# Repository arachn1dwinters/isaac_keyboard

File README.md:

# isaac_keyboard
This repository contains the .gerber files (which can be sent to a service like JPLPCB for manufacture) and the kicad files themselves for customization purposes.

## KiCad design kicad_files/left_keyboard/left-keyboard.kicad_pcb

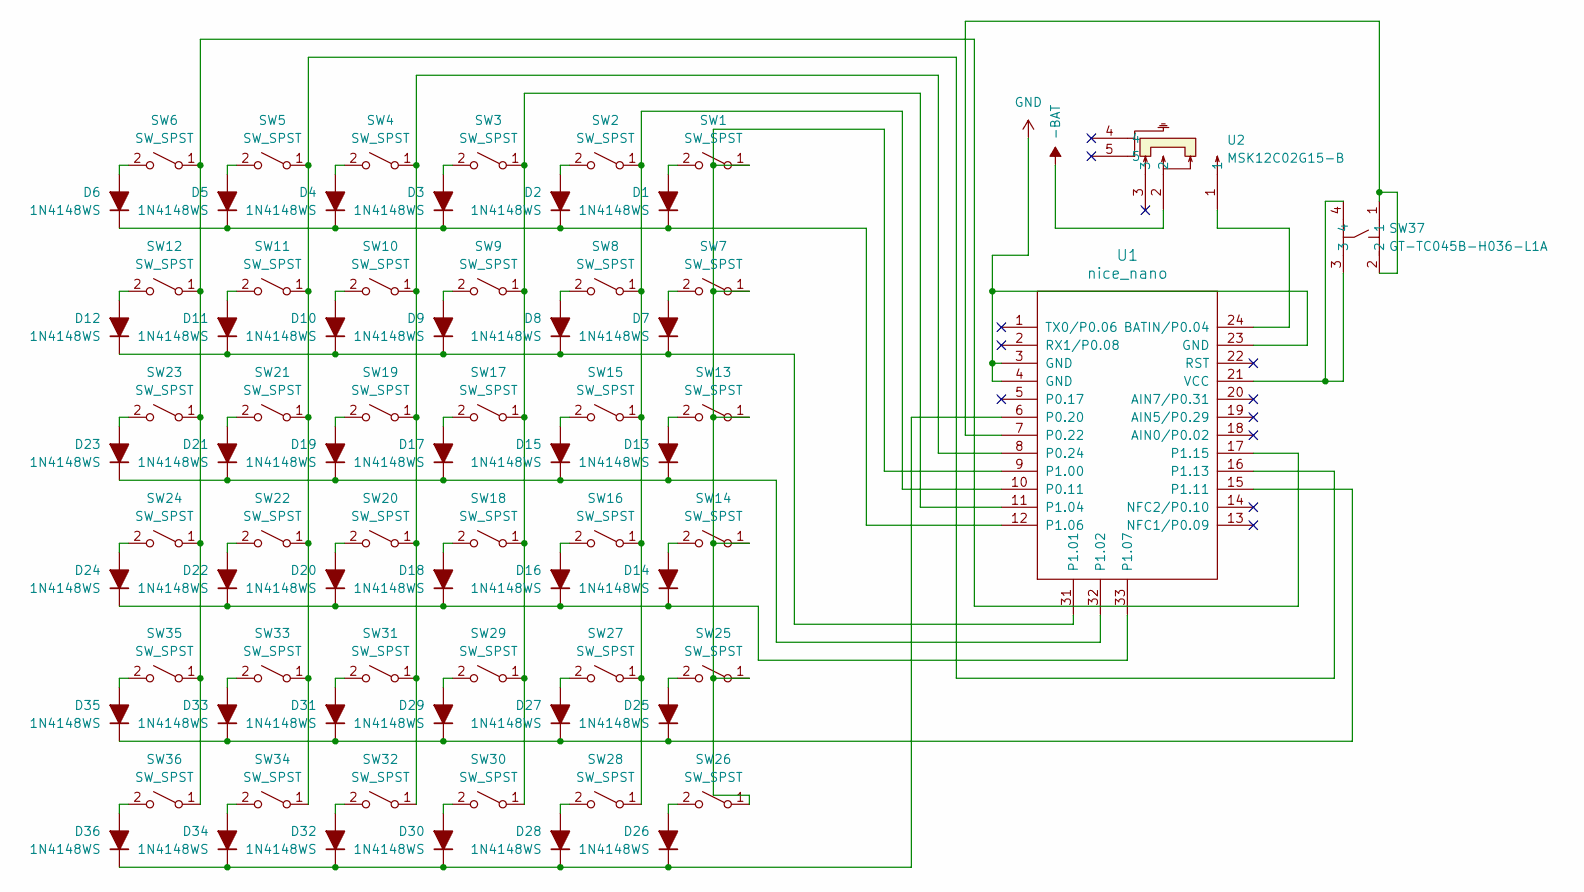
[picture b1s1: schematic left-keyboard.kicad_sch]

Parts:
D1, D2, D3, D4, D5, D6, D7, D8, D9, D10, D11, D12, D13, D14, D15, D16, D17, D18, D19, D20, D21, D22, D23, D24, D25, D26, D27, D28, D29, D30, D31, D32, D33, D34, D35, D36: 1N4148WS; D_SOD-323
SW1, SW2, SW3, SW4, SW5, SW6, SW7, SW8, SW9, SW10, SW11, SW12, SW13, SW14, SW15, SW16, SW17, SW18, SW19, SW20, SW21, SW22, SW23, SW24, SW25, SW26, SW27, SW28, SW29, SW30, SW31, SW32, SW33, SW34, SW35, SW36: SW_SPST; SW_Hotswap_Kailh_Choc_V1V2
SW37: GT-TC045B-H036-L1A; SW-SMD_4P-L3.5-W3.0-P1.6-LS4.6_K2-1821SH-A4SW-06; LCSC Part C778148
U1: nice_nano
U2: MSK12C02G15-B; SW-SMD_MSK12C02G15-B; LCSC Part C22435661

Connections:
-BAT: U2.2
GND: U1.3 (GND), U1.4 (GND), U1.23 (GND)
unnamed: D1.2 (A), SW1.2 (B)
unnamed: D1.1 (K), D2.1 (K), D3.1 (K), D4.1 (K), D5.1 (K), D6.1 (K), U1.12 (P1.06)
unnamed: D2.2 (A), SW2.2 (B)
unnamed: D3.2 (A), SW3.2 (B)
unnamed: D4.2 (A), SW4.2 (B)
unnamed: D5.2 (A), SW5.2 (B)
unnamed: D6.2 (A), SW6.2 (B)
unnamed: D7.2 (A), SW7.2 (B)
unnamed: D8.2 (A), SW8.2 (B)
unnamed: D9.2 (A), SW9.2 (B)
unnamed: D10.2 (A), SW10.2 (B)
unnamed: D7.1 (K), D8.1 (K), D9.1 (K), D10.1 (K), D11.1 (K), D12.1 (K), U1.31 (P1.01)
unnamed: D11.2 (A), SW11.2 (B)
unnamed: D12.2 (A), SW12.2 (B)
unnamed: D13.2 (A), SW13.2 (B)
unnamed: D13.1 (K), D15.1 (K), D17.1 (K), D19.1 (K), D21.1 (K), D23.1 (K), U1.32 (P1.02)
unnamed: D14.2 (A), SW14.2 (B)
unnamed: D14.1 (K), D16.1 (K), D18.1 (K), D20.1 (K), D22.1 (K), D24.1 (K), U1.33 (P1.07)
unnamed: D15.2 (A), SW15.2 (B)
unnamed: D16.2 (A), SW16.2 (B)
unnamed: D17.2 (A), SW17.2 (B)
unnamed: D18.2 (A), SW18.2 (B)
unnamed: D19.2 (A), SW19.2 (B)
unnamed: D20.2 (A), SW20.2 (B)
unnamed: D21.2 (A), SW21.2 (B)
unnamed: D22.2 (A), SW22.2 (B)
unnamed: D23.2 (A), SW23.2 (B)
unnamed: D24.2 (A), SW24.2 (B)
unnamed: D25.2 (A), SW25.2 (B)
unnamed: D25.1 (K), D27.1 (K), D29.1 (K), D31.1 (K), D33.1 (K), D35.1 (K), U1.15 (P1.11)
unnamed: D26.2 (A), SW26.2 (B)
unnamed: D26.1 (K), D28.1 (K), D30.1 (K), D32.1 (K), D34.1 (K), D36.1 (K), U1.6 (P0.20)
unnamed: D27.2 (A), SW27.2 (B)
unnamed: D28.2 (A), SW28.2 (B)
unnamed: D29.2 (A), SW29.2 (B)
unnamed: D30.2 (A), SW30.2 (B)
unnamed: D31.2 (A), SW31.2 (B)
unnamed: D32.2 (A), SW32.2 (B)
unnamed: D33.2 (A), SW33.2 (B)
unnamed: D34.2 (A), SW34.2 (B)
unnamed: D35.2 (A), SW35.2 (B)
unnamed: D36.2 (A), SW36.2 (B)
unnamed: SW1.1 (A), SW7.1 (A), SW13.1 (A), SW14.1 (A), SW25.1 (A), SW26.1 (A), U1.9 (P1.00)
unnamed: SW4.1 (A), SW10.1 (A), SW19.1 (A), SW20.1 (A), SW31.1 (A), SW32.1 (A), U1.8 (P0.24)
unnamed: SW5.1 (A), SW11.1 (A), SW21.1 (A), SW22.1 (A), SW33.1 (A), SW34.1 (A), U1.16 (P1.13)
unnamed: SW6.1 (A), SW12.1 (A), SW23.1 (A), SW24.1 (A), SW35.1 (A), SW36.1 (A), U1.17 (P1.15)
unnamed: SW2.1 (A), SW8.1 (A), SW15.1 (A), SW16.1 (A), SW27.1 (A), SW28.1 (A), U1.10 (P0.11)
unnamed: SW3.1 (A), SW9.1 (A), SW17.1 (A), SW18.1 (A), SW29.1 (A), SW30.1 (A), U1.11 (P1.04)
unnamed: U1.24 (BATIN/P0.04), U2.1
unnamed: SW37.1, SW37.2, U1.7 (P0.22)
unnamed: SW37.3, SW37.4, U1.21 (VCC)

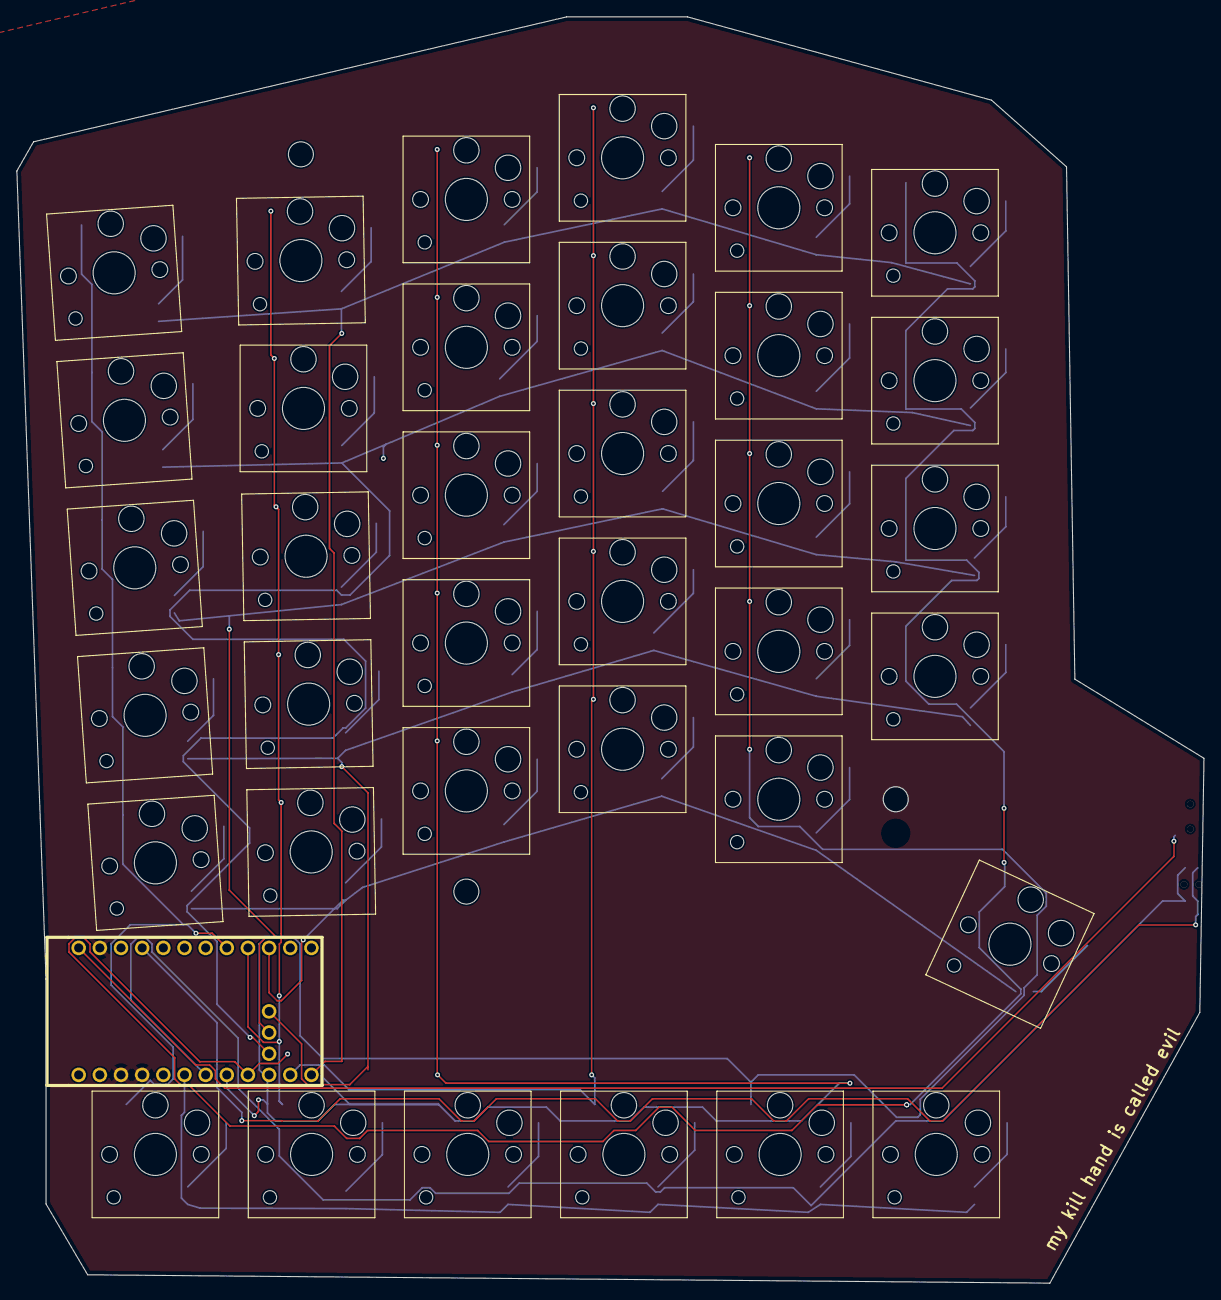
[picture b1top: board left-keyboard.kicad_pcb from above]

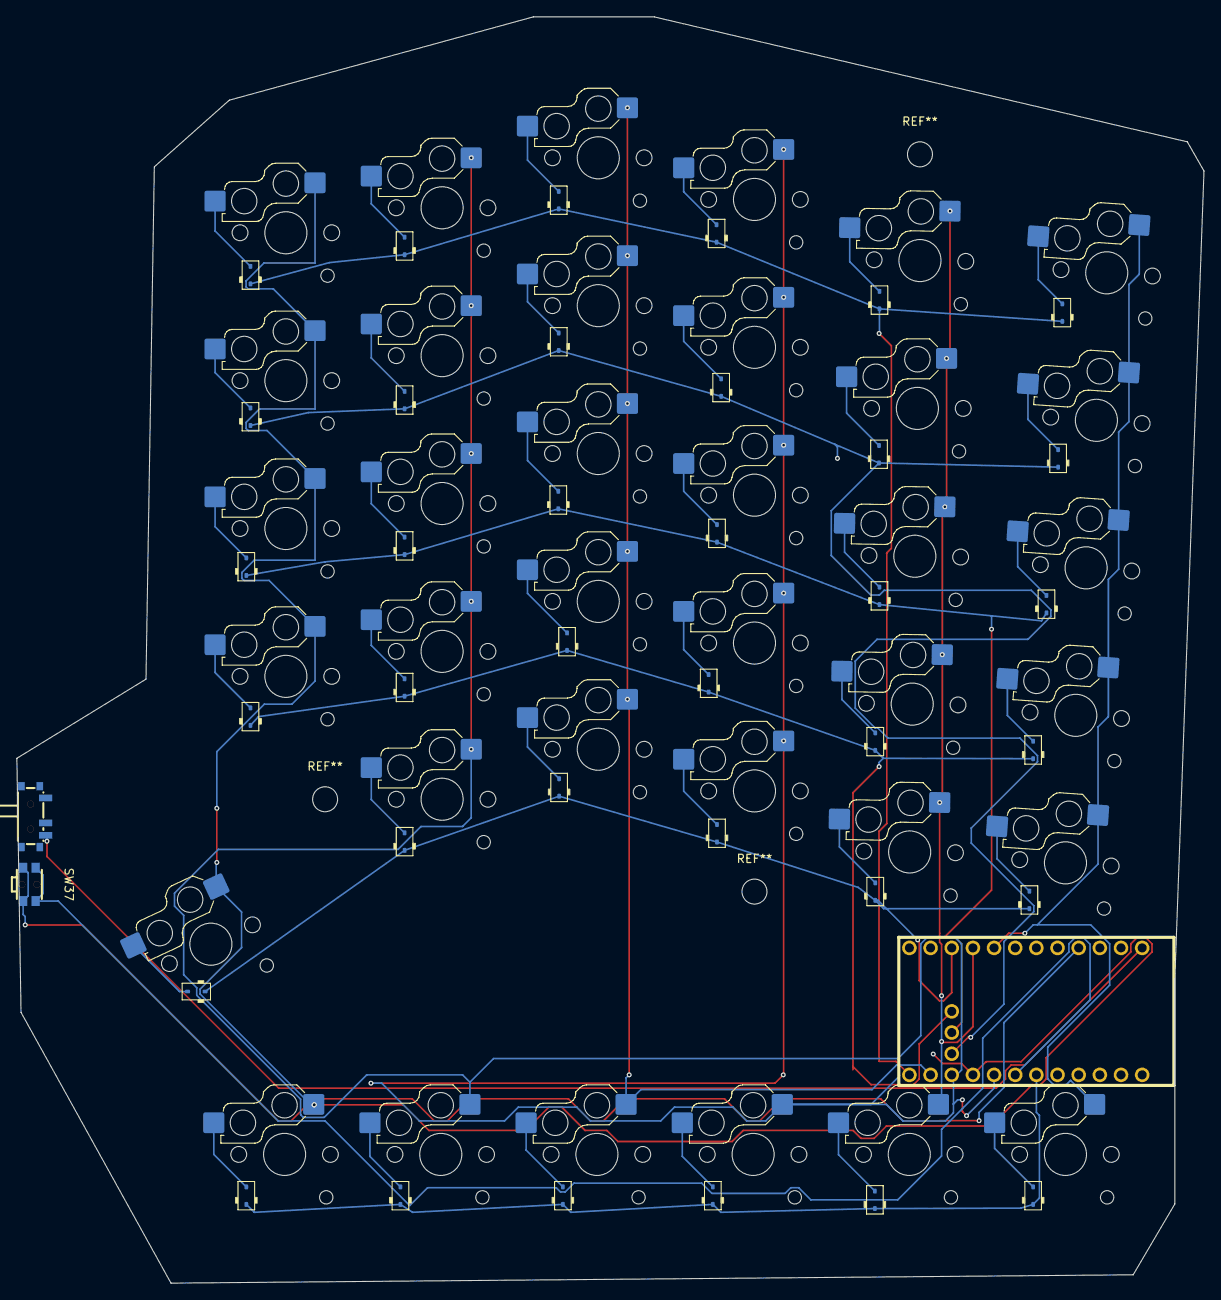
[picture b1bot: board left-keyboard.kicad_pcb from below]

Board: 2 copper layers, 142.5 x 152.0 mm, 75 parts (38 on the bottom side), 52 nets.

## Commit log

2025-10-21 Remove description from README.md
2025-10-21 Add Kicad Files
2025-10-21 Update README
    Added description of repository contents.
2025-10-23 Add .gerber files
2025-10-23 Remove poorly formatted .gerber files
2025-10-23 Add better gerber zips
